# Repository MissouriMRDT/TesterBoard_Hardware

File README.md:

# TesterBoard_Hardware
Hardware for the tester device.

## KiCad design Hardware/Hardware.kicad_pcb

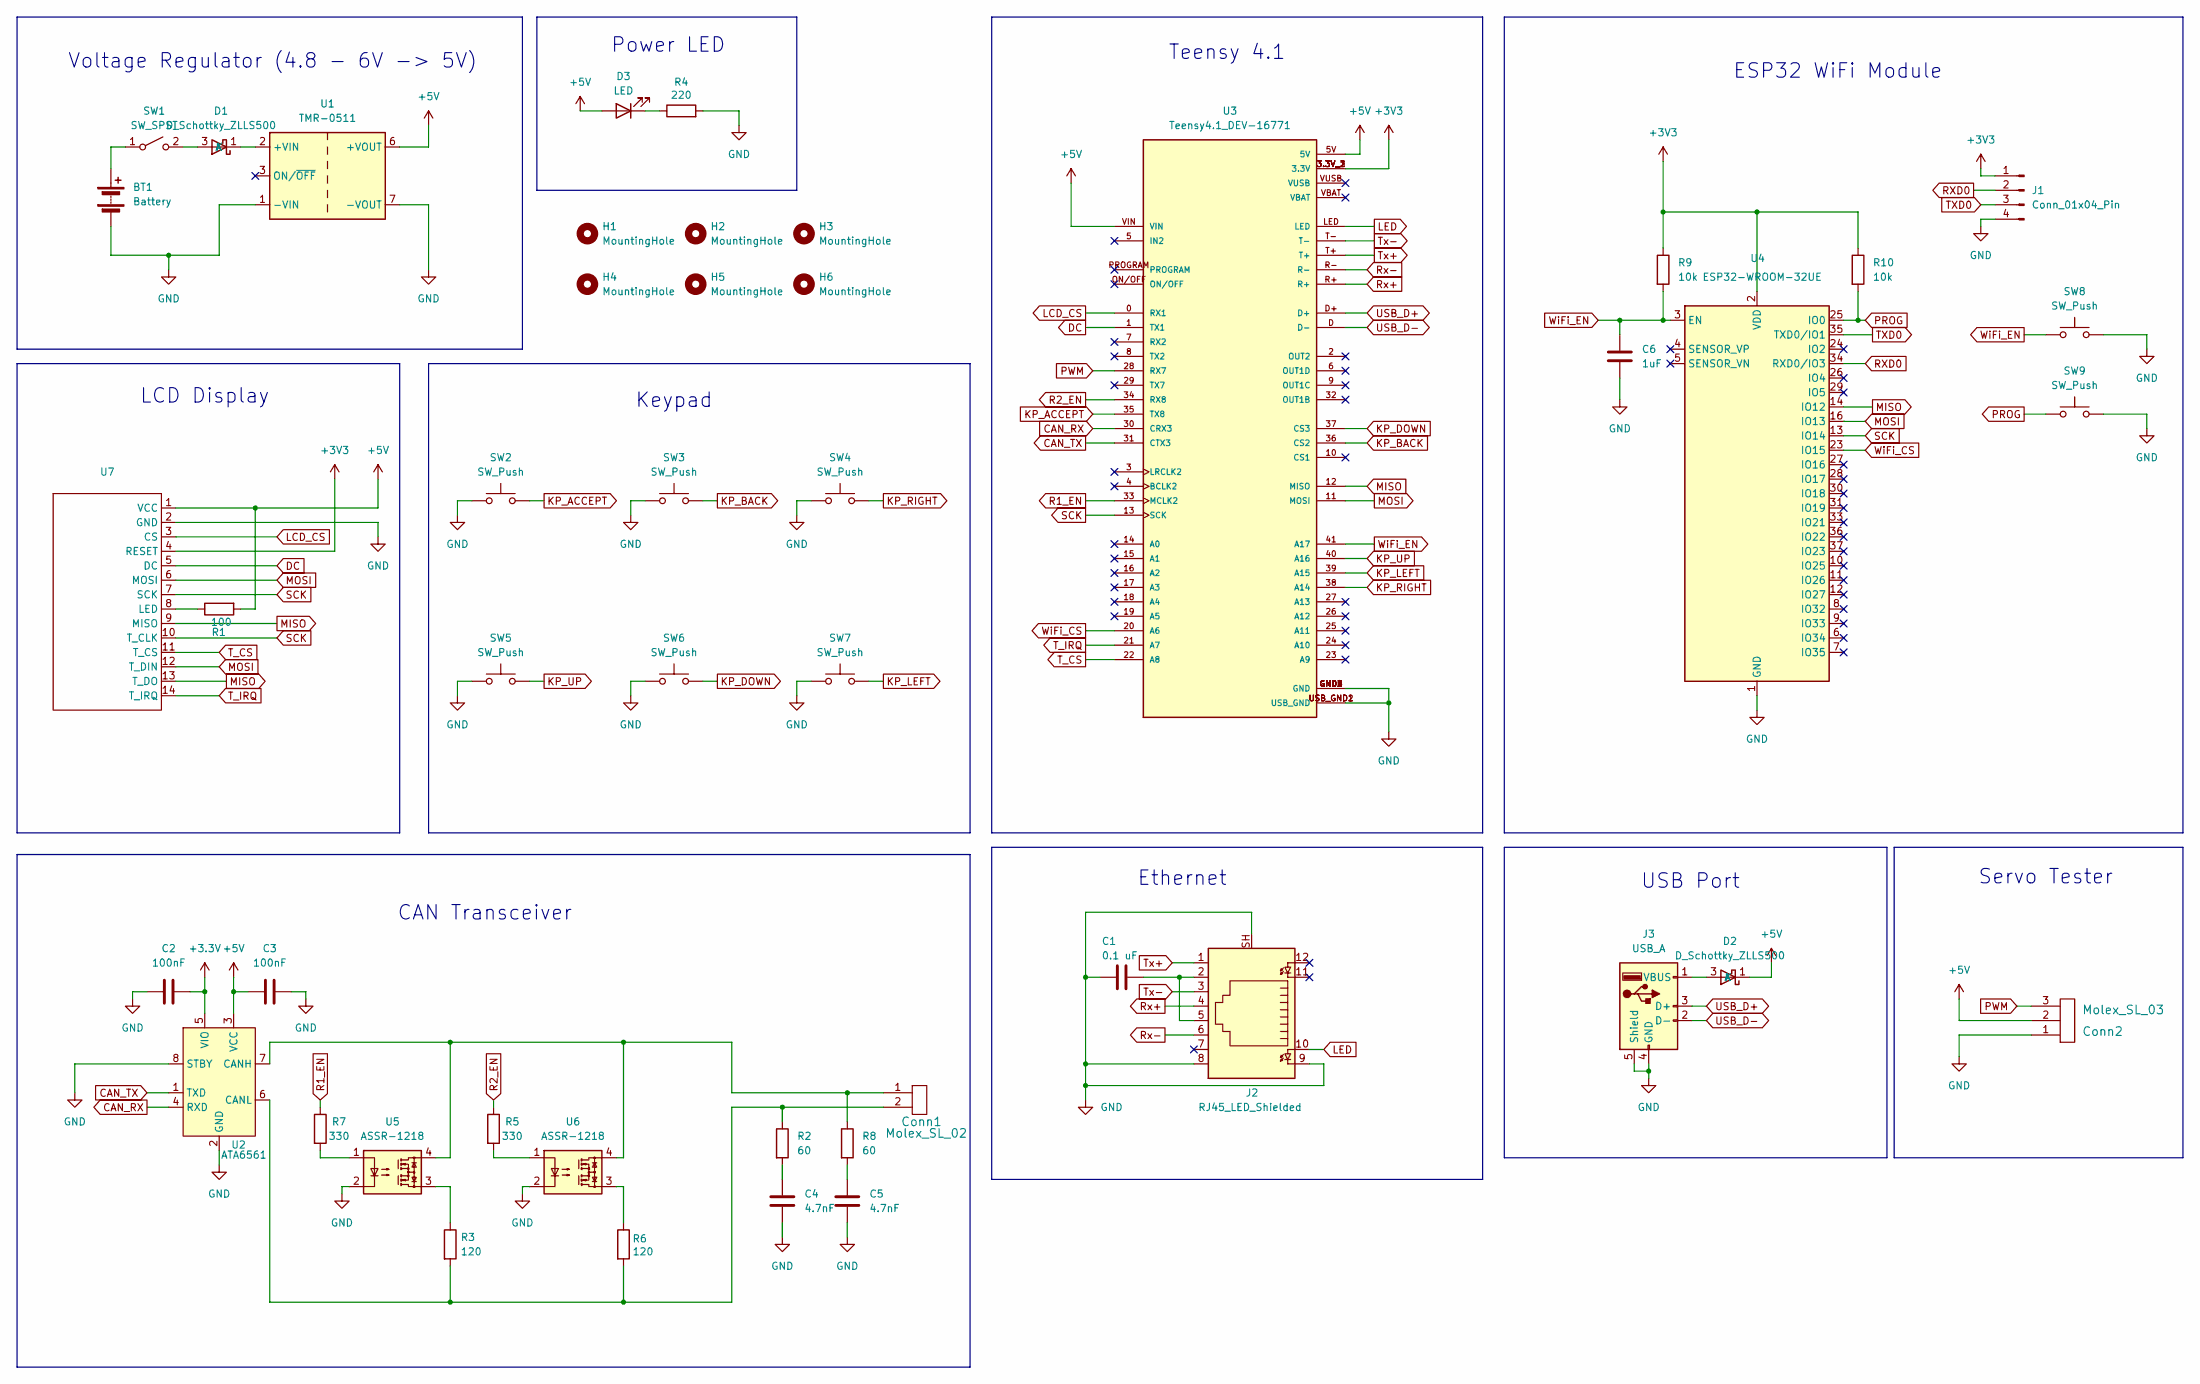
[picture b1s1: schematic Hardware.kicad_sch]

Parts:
BT1: Battery; Bat_4xAA_MP000327
C1: 0.1 uF; C_0603_1608Metric_Pad1.08x0.95mm_HandSolder
C2, C3: 100nF; C_0603_1608Metric_Pad1.08x0.95mm_HandSolder
C4, C5: 4.7nF; C_0603_1608Metric_Pad1.08x0.95mm_HandSolder
C6: 1uF; C_0603_1608Metric_Pad1.08x0.95mm_HandSolder
Conn1: Molex_SL_02; JST_PH_B2B-PH-K_1x02_P2.00mm_Vertical
Conn2: Molex_SL_03; JST_PH_B3B-PH-K_1x03_P2.00mm_Vertical
D1, D2: D_Schottky_ZLLS500
D3: LED; LED_D5.0mm
H1, H2, H3, H4, H5, H6: MountingHole; 4_40_Hole
J1: Conn_01x04_Pin; PinHeader_1x04_P2.54mm_Vertical
J2: RJ45_LED_Shielded; RJ45_Teensy
J3: USB_A; USB_A_Molex_67643_Horizontal
R1: 100; R_0603_1608Metric_Pad0.98x0.95mm_HandSolder
R2, R8: 60; R_0603_1608Metric_Pad0.98x0.95mm_HandSolder
R3, R6: 120; R_0603_1608Metric_Pad0.98x0.95mm_HandSolder
R4: 220; R_0603_1608Metric_Pad0.98x0.95mm_HandSolder
R5, R7: 330; R_0603_1608Metric_Pad0.98x0.95mm_HandSolder
R9, R10: 10k; R_0603_1608Metric_Pad0.98x0.95mm_HandSolder
SW1: SW_SPST; SW_Slide_SPDT_Angled_CK_OS102011MA1Q
SW2, SW3, SW4, SW5, SW6, SW7: SW_Push; SW_SPST_TL3301
SW8, SW9: SW_Push; SW_SPST_TL3305A
U1: TMR-0511; Converter_DCDC_TRACO_TMR-xxxx_THT
U2: ATA6561; SOIC-8_3.9x4.9mm_P1.27mm
U3: Teensy4.1_DEV-16771; Teensy_4_1; PARTREV 4.1
U4: ESP32-WROOM-32UE
U5, U6: ASSR-1218; SO-4_4.4x4.3mm_P2.54mm
U7: DISPLAY_ILI9341_TOUCH_32

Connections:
+3.3V: C2.1, U2.5 (VIO)
+3V3: J1.1, R9.1, R10.1, U3.3.3V_1 (3.3V), U3.3.3V_2 (3.3V), U3.3.3V_3 (3.3V), U4.2 (VDD), U7.4 (RESET)
+5V: C3.1, Conn2.2, D2.1 (K), D3.2 (A), R1.2, U1.6 (+VOUT), U2.3 (VCC), U3.5V, U3.VIN, U7.1 (VCC)
CAN_RX: U2.4 (RXD), U3.30 (CRX3)
CAN_TX: U2.1 (TXD), U3.31 (CTX3)
DC: U3.1 (TX1), U7.5 (DC)
GND: BT1.2 (-), C1.2, C2.2, C3.2, C4.2, C5.2, C6.2, Conn2.1, J1.4, J2.8, J2.9, J2.SH, J3.4 (GND), J3.5 (Shield), R4.2, SW2.1, SW3.1, SW4.1, SW5.1, SW6.1, SW7.1, SW8.2, SW9.2, U1.1 (-VIN), U1.7 (-VOUT), U2.2 (GND), U2.8 (STBY), U3.GND1 (GND), U3.GND2 (GND), U3.GND3 (GND), U3.GND4 (GND), U3.GND5 (GND), U3.USB_GND1 (USB_GND), U3.USB_GND2 (USB_GND), U4.1 (GND), U4.15 (GND), U4.38 (GND), U4.39 (GND), U5.2, U6.2, U7.2 (GND)
KP_ACCEPT: SW2.2, U3.35 (TX8)
KP_BACK: SW3.2, U3.36 (CS2)
KP_DOWN: SW6.2, U3.37 (CS3)
KP_LEFT: SW7.2, U3.39 (A15)
KP_RIGHT: SW4.2, U3.38 (A14)
KP_UP: SW5.2, U3.40 (A16)
LCD_CS: U3.0 (RX1), U7.3 (CS)
LED: J2.10, U3.LED
MISO: U3.12 (MISO), U4.14 (IO12), U7.9 (MISO), U7.13 (T_DO)
MOSI: U3.11 (MOSI), U4.16 (IO13), U7.6 (MOSI), U7.12 (T_DIN)
unnamed: BT1.1 (+), SW1.1 (A)
unnamed: C1.1, J2.2, J2.5
unnamed: C4.1, R2.2
unnamed: C5.1, R8.2
unnamed: D1.3 (A), SW1.2 (B)
unnamed: D1.1 (K), U1.2 (+VIN)
unnamed: D2.3 (A), J3.1 (VBUS)
unnamed: D3.1 (K), R4.1
unnamed: R3.1, U5.3
unnamed: R5.2, U6.1
unnamed: R6.1, U6.3
unnamed: R7.2, U5.1
unnamed: Conn1.1, R8.1, U2.7 (CANH), U5.4, U6.4
unnamed: Conn1.2, R2.1, R3.2, R6.2, U2.6 (CANL)
unnamed: R1.1, U7.8 (LED)
PROG: R10.2, SW9.1, U4.25 (IO0)
PWM: Conn2.3, U3.28 (RX7)
R1_EN: R7.1, U3.33 (MCLK2)
R2_EN: R5.1, U3.34 (RX8)
RXD0: J1.2, U4.34 (RXD0/IO3)
Rx+: J2.4, U3.R+
Rx-: J2.6, U3.R-
SCK: U3.13 (SCK), U4.13 (IO14), U7.7 (SCK), U7.10 (T_CLK)
TXD0: J1.3, U4.35 (TXD0/IO1)
T_CS: U3.22 (A8), U7.11 (T_CS)
T_IRQ: U3.21 (A7), U7.14 (T_IRQ)
Tx+: J2.1, U3.T+
Tx-: J2.3, U3.T-
USB_D+: J3.3 (D+), U3.D+
USB_D-: J3.2 (D-), U3.D (D-), U3.D-
WiFi_CS: U3.20 (A6), U4.23 (IO15)
WiFi_EN: C6.1, R9.2, SW8.1, U3.41 (A17), U4.3 (EN)

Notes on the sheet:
LCD Display
Servo Tester
Power LED
Teensy 4.1
Voltage Regulator (4.8 - 6V -> 5V)
ESP32 WiFi Module
USB Port
Keypad
Ethernet
CAN Transceiver

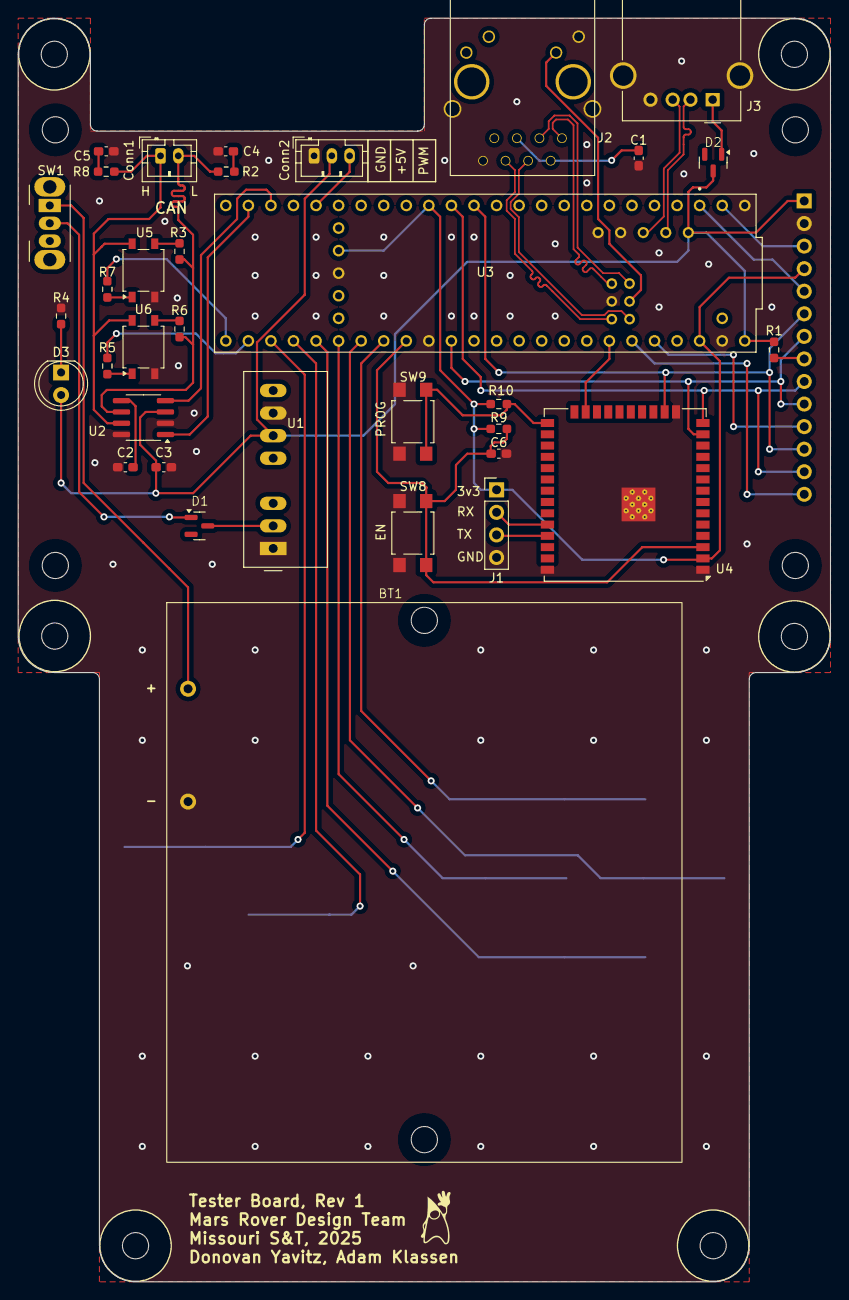
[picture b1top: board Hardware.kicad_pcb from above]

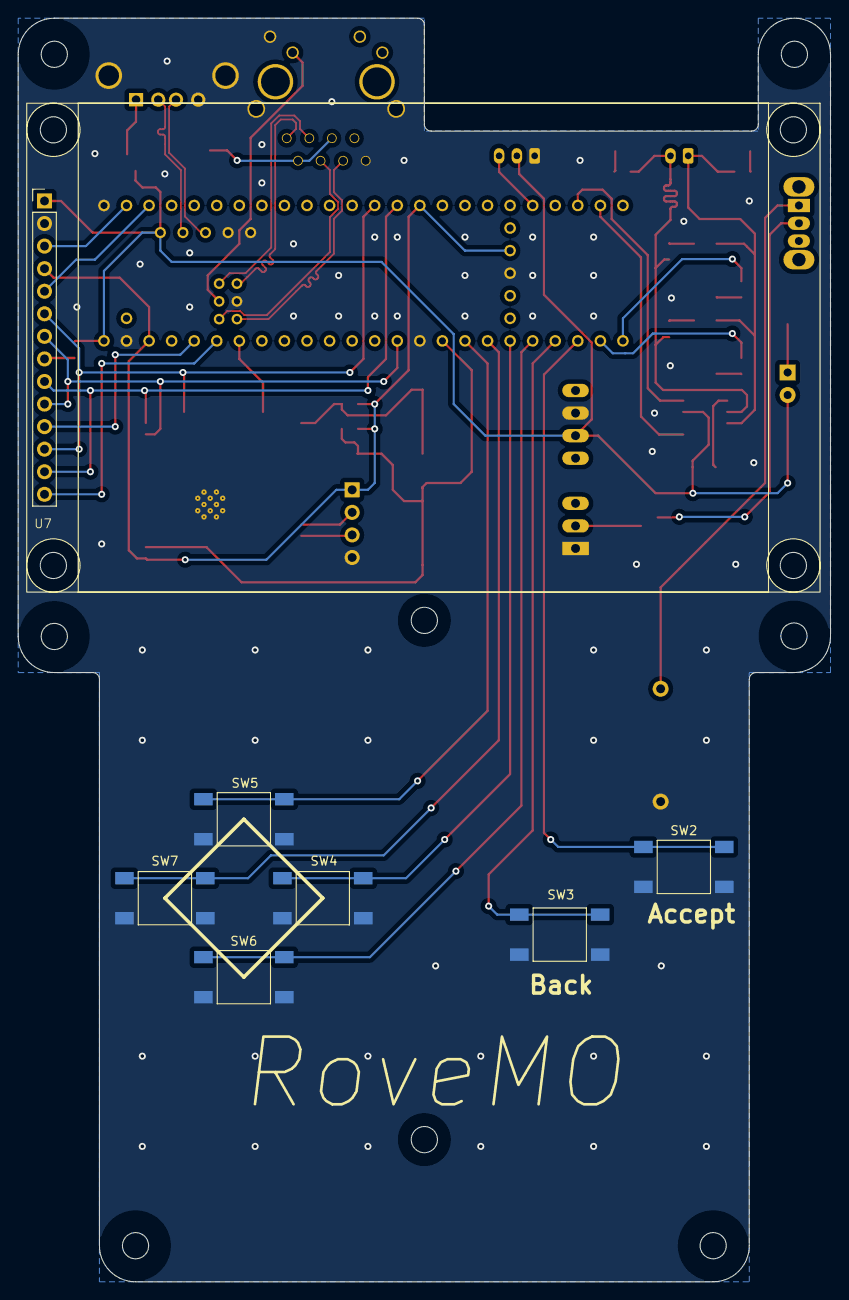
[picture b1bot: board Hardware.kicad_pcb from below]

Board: 2 copper layers, 91.4 x 142.2 mm, 47 parts (7 on the bottom side), 49 nets.

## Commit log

2024-09-25 Made Project File
2024-09-25 Placed Teensy
2024-09-25 Added things (very nice)
2024-09-29 connected teensy pins to LCD socket
2024-09-30 Fixed schematic errors, mapped touchscreen pins for the lcd
2024-10-05 Added battery/voltage regulator
2024-10-05 Added Labels
2024-10-07 moved things around to make space for CAN tranceiver and keypad
2024-10-12 Added CAN tranceiver and keypad
2024-10-30 added usb port and wifi module
2024-10-31 started pcb layout
2024-10-31 fixed schematic for layout
2024-10-31 Create sym-lib-table
2024-10-31 Create fp-lib-table
2024-11-01 Added some traces
2024-11-01 added mounting holes and fixed stuff
2024-11-03 finished up the layout and cleaned up libraries
2024-11-04 swapped buck and esp32 to make traces shorter
2024-11-05 added 3d model for touch screen
2024-11-06 changed battery case to through-hole pcb mount
2024-11-14 added some data sheets
2024-11-15 fixed silkscreens and added servo tester
2024-11-15 fixed skew on ethernet traces
2024-11-15 added Gerbs
